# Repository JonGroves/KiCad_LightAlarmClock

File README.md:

The printed circuit board (PCB) layout for use in the Light Alarm Clock Project. 

This includes the copper traces, solder mask, and silk screen layers, in addition to component selection and layout.

3D Render
 
Schematic

Front Copper layer

# Firmware
The corresponding firmware can be found [here](https://github.com/JonGroves/ESP8266_LightAlarmClock).

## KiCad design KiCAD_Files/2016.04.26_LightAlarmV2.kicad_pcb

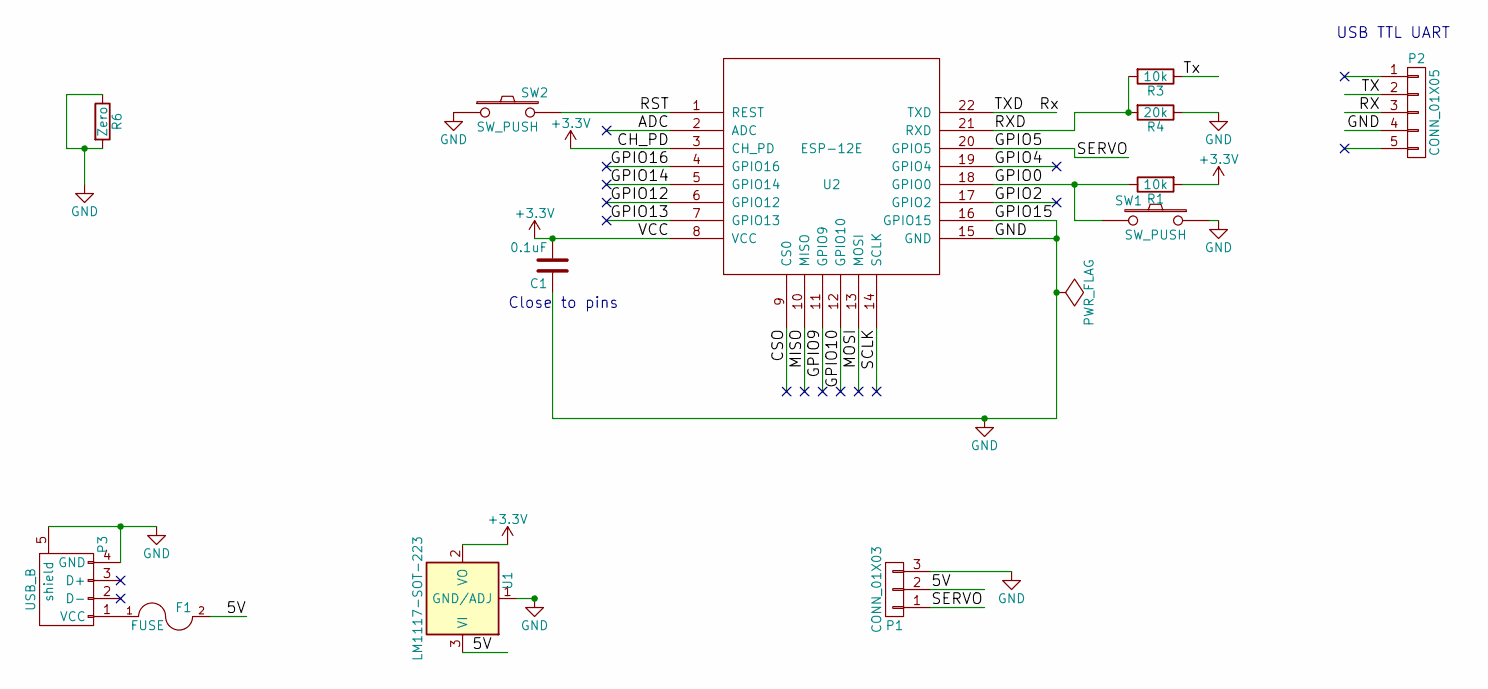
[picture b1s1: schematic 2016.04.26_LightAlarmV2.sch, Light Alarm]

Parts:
C1: 0.1uF; R_0805_HandSoldering
F1: FUSE; R_1812_HandSoldering
P1: CONN_01X03; Pin_Header_Angled_1x03
P2: CONN_01X05; Pin_Header_Angled_1x05
P3: USB_B; USB_Mini-B
R1, R3: 10k; R_0805_HandSoldering
R4: 20k; R_0805_HandSoldering
R6: Zero; R_1206_HandSoldering
SW1, SW2: SW_PUSH; SW_SPST_EVPBF
U1: LM1117-SOT-223; SOT-223
U2: ESP-12E

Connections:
+3V3: C1.2, R1.2, U1.2 (VO), U2.3 (CH_PD), U2.8 (VCC)
/5V: F1.2, P1.2, U1.3 (VI)
/ADC: U2.2 (ADC)
/CSO: U2.9 (CS0)
/GPIO0: R1.1, SW1.2, U2.18 (GPIO0)
/GPIO2: U2.17 (GPIO2)
/GPIO4: U2.19 (GPIO4)
/GPIO5: P1.1, U2.20 (GPIO5)
/GPIO9: U2.11 (GPIO9)
/GPIO10: U2.12 (GPIO10)
/GPIO12: U2.6 (GPIO12)
/GPIO13: U2.7 (GPIO13)
/GPIO14: U2.5 (GPIO14)
/GPIO16: U2.4 (GPIO16)
/MISO: U2.10 (MISO)
/MOSI: U2.13 (MOSI)
/RST: SW2.2, U2.1 (REST)
/RX: P2.3, U2.22 (TXD)
/RXD: R3.2, R4.2, U2.21 (RXD)
/SCLK: U2.14 (SCLK)
/TX: P2.2, R3.1
GND: C1.1, P1.3, P2.4, P3.4 (GND), P3.5 (shield), R4.1, R6.1, R6.2, SW1.1, SW2.1, U1.1 (GND/ADJ), U2.15 (GND), U2.16 (GPIO15)
unnamed: F1.1, P3.1 (VCC)

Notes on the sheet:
USB TTL UART
Close to pins

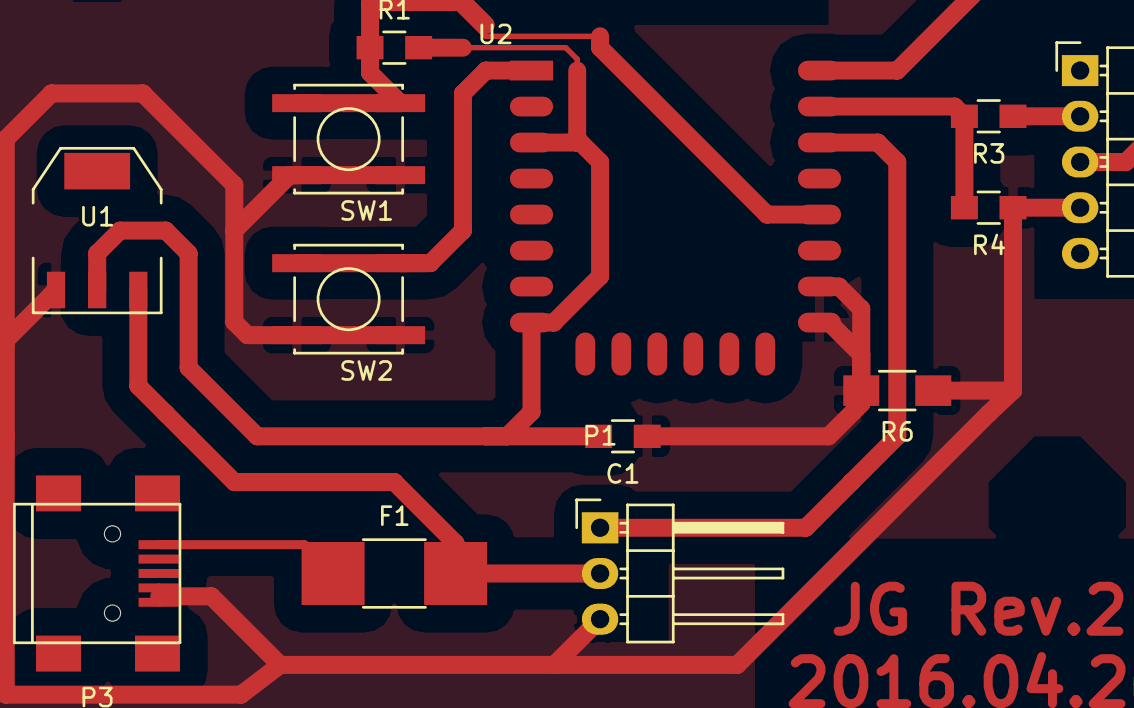
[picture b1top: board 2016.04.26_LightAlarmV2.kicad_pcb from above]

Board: 2 copper layers, 13 parts (0 on the bottom side), 10 nets.

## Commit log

2016-04-27 Added button to allow for reflashing firmware
2020-08-19 Added more images to README
2020-08-24 Linked to corresponding firmware
